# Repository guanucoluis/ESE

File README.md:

# ESE

Especialización en Sistemas Embebidos
============

En este repositorio se agregan algunos de los prácticos y proyectos del Posgrado.

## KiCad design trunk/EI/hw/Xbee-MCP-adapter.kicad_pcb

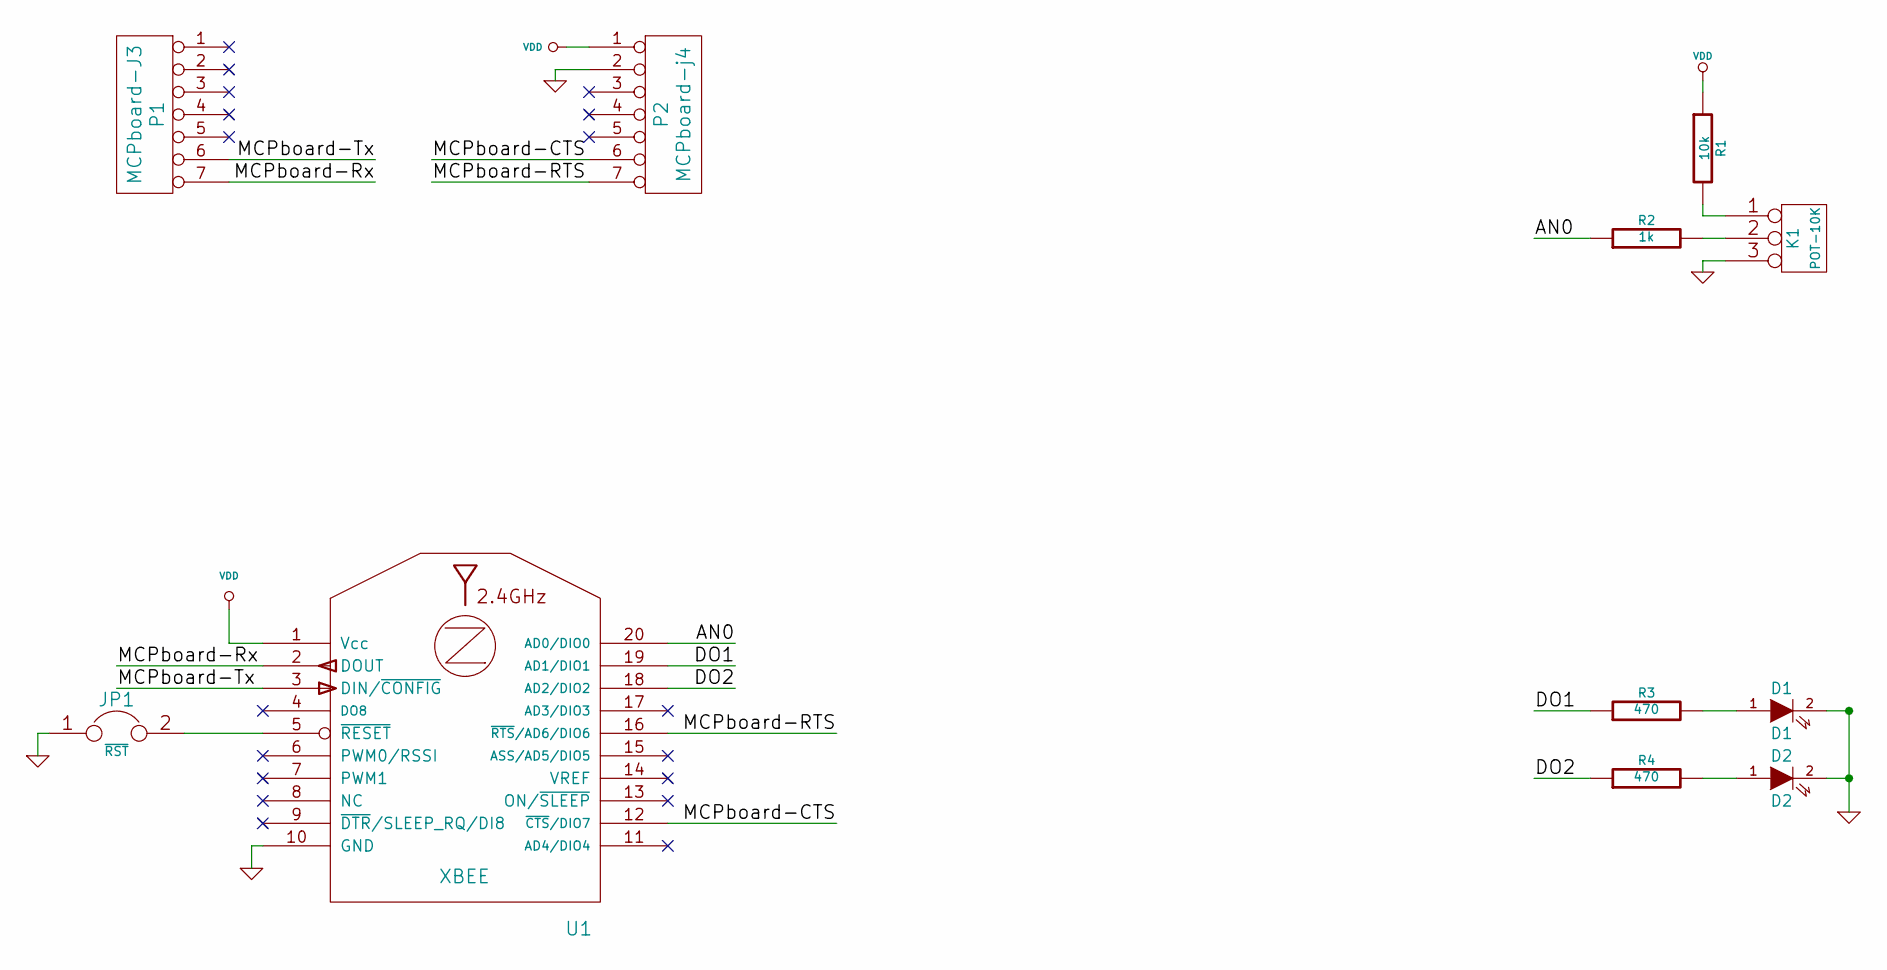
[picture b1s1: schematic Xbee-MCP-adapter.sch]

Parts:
D1: D1
D2: D2
JP1: ~RST
K1: POT-10K
P1: MCPboard-J3
P2: MCPboard-j4
R1: 10k
R2: 1k
R3, R4: 470
U1: XBEE

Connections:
/AN0: R2.1, U1.20 (AD0/DIO0)
/DO1: R3.1, U1.19 (AD1/DIO1)
/DO2: R4.1, U1.18 (AD2/DIO2)
/MCPboard-CTS: P2.6, U1.12 (~CTS~/DIO7)
/MCPboard-RTS: P2.7, U1.16 (~RTS~/AD6/DIO6)
/MCPboard-Rx: P1.7, U1.2 (DOUT)
/MCPboard-Tx: P1.6, U1.3 (DIN/~CONFIG)
GND: D1.2 (K), D2.2 (K), JP1.1, K1.3, P2.2, U1.10 (GND)
unnamed: K1.1, R1.2
unnamed: K1.2 (PM), R2.2
unnamed: D2.1 (A), R4.2
unnamed: D1.1 (A), R3.2
unnamed: JP1.2, U1.5 (~RESET)
VDD: P2.1, R1.1, U1.1 (Vcc)

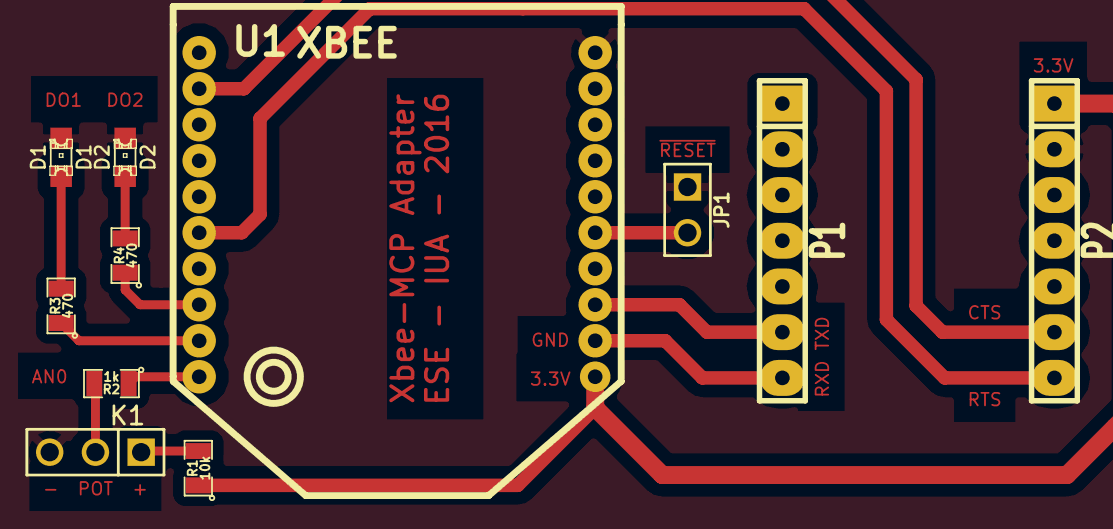
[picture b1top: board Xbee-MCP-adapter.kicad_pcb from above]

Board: 2 copper layers, 11 parts (0 on the bottom side), 14 nets.

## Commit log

2015-05-30 Se crea directorio principal de trabajo
2015-05-30 Cambios menores
2015-06-15 Commit test
2015-06-15 New changes
2015-06-15 Agrego directorio de trabajo para el TP1
2015-06-16 [REQ] Agrego análisis de requerimientos (alto-nivel)
2015-06-16 [REQ] Envíamos correo sober consultas en los requerimientos
2015-06-18 [REQ] Agrego conceptos de Caso de Uso y genero algunos de estos items
2015-06-23 [RAD][DOC] Se agregan contenidos sobre documentacion del TP
2015-06-30 [ANA] Se agregan los resultados de los diagramas de clases de mdioli
2015-07-02 [ANA][IMP] Agrego archivos de Análisis e Implementación
2015-07-02 [IMP] Cree carpeta para compilar arduino
2015-08-28 [SI][TP][REQ] Agrego primera versión de los requerimientos
2015-08-29 Agrego links de referencias
2016-03-04 [Alg] Agrego documentos de la revisión del paper p1-astrachan.pdf
2016-03-04 cambios en reuniones
2016-03-04 cambios en reporte
2016-03-08 Cambios en report
2016-03-09 agrego contenido
2016-03-10 Nuevos cambios
2016-03-11 1ra versión final
2016-03-20 Primera versión del paper -- Servicios REST
2016-03-30 Agrego enlace de referencia y notas sobre REST
2016-04-06 Referencias de SOA y REST
2016-04-07 agrego contenido sobre REST y ref
2016-04-12 version con SOAP y REST (sin conclusiones)
2016-04-15 version final para enviar
2016-04-18 commit initial version, working in Eclipse.
2016-04-20 borro archivos de eclipse
2016-04-21 cambios en directorio de SD y agrego beamer para presentacion
2016-04-21 elimino directorio fuera del trunk
2016-04-22 agregado implementacion Santiago
2016-04-22 Se implementaron request y response
2016-04-23 cambios en la clase del sabado
2016-04-26 primera version estable funcional
2016-04-27 Correcciones menores del paper
2016-04-28 correccion de linea carry y nueva linea
2016-04-29 Agrego la primer versión final de la presentación y meto cambios mínimos del paper
2016-04-29 Cambios mínimos (gramaticales)
2016-04-29 Cambio roden de diapositivas
2016-04-29 Cambio mínimo
2016-04-29 Correcciones gramaticales
2016-04-29 Agrego un punto mas de REST
2016-04-29 agrego zip con calculadora restful
2016-04-30 agrgo src finales de http server
2016-05-24 Elimino archivos de compilación de eclipse y actualizo paper
2016-05-25 Comienzamos con el TP de DSP
2016-05-28 Notas sobre el TP y diagramas
2016-05-28 Corrección sobre las direcciónes de los puertos del diagrama en bloque general
2016-06-24 Agrego primer borrador de reporte.
2016-08-25 Agrego directorio de materia Entornos Inalámbricos (EI)
2016-08-26 La primera version de la placa Xbee-MCP-adapter
2016-08-26 placa final
2016-08-29 Agregando puntos del TP en el reporte
2016-08-30 Puntos 2-6 terminados
2016-09-01 Cambios de formato en documento
2016-09-02 Agregado el punto 1, 7 y 8
2016-09-05 Escritura de los últimos puntos
2016-09-07 puntos 11-12 en proceso
2016-09-09 Informe final
2016-09-09 Informe final (correciones de caracteres
2016-09-12 Informe final - última integración con punto 1 (propagación)
2016-09-12 Informe final - última integración
2016-10-27 Agrego directorio IP
2016-10-27 actualización informe
